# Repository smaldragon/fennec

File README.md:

# fennec
An Homebrew computer using the 65c02 CPU.

All assembly code is built using my custom assembler built for personal hobby use, [CapyAsm](https://github.com/smaldragon/CapyASM), these two projects are closely linked and build off eachother, *with both* currently being in a early alpha state subject to bugs and regular breaking changes.

Documentation for the machine is located on its wiki at https://fennec6502.miraheze.org/

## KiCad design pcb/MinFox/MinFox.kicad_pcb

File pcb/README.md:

# GENERAL WARNING

These are various kicad projects developed over the course of this project, before taking a look at these it is extremely important that you understand the following:

* These projects are largely untested
* These projects were designed by a very clueless self-taught hobbyist
* I do not recommend using any of these for any purpose without scrutiny

## The projects

### 40key BreadKeys

A 40% mechanical keyboard matrix (8x5) designed to be hooked up to a breadboard via DuPont jumpers.

### MinFox 

A minimal expandable 65c02 sbc built for debugging peripherals, it contains ROM, RAM and 6 "slot select" lines (same terminology as the Fennec) that allow easily adding expansion chips without extra hardress decoding logic.

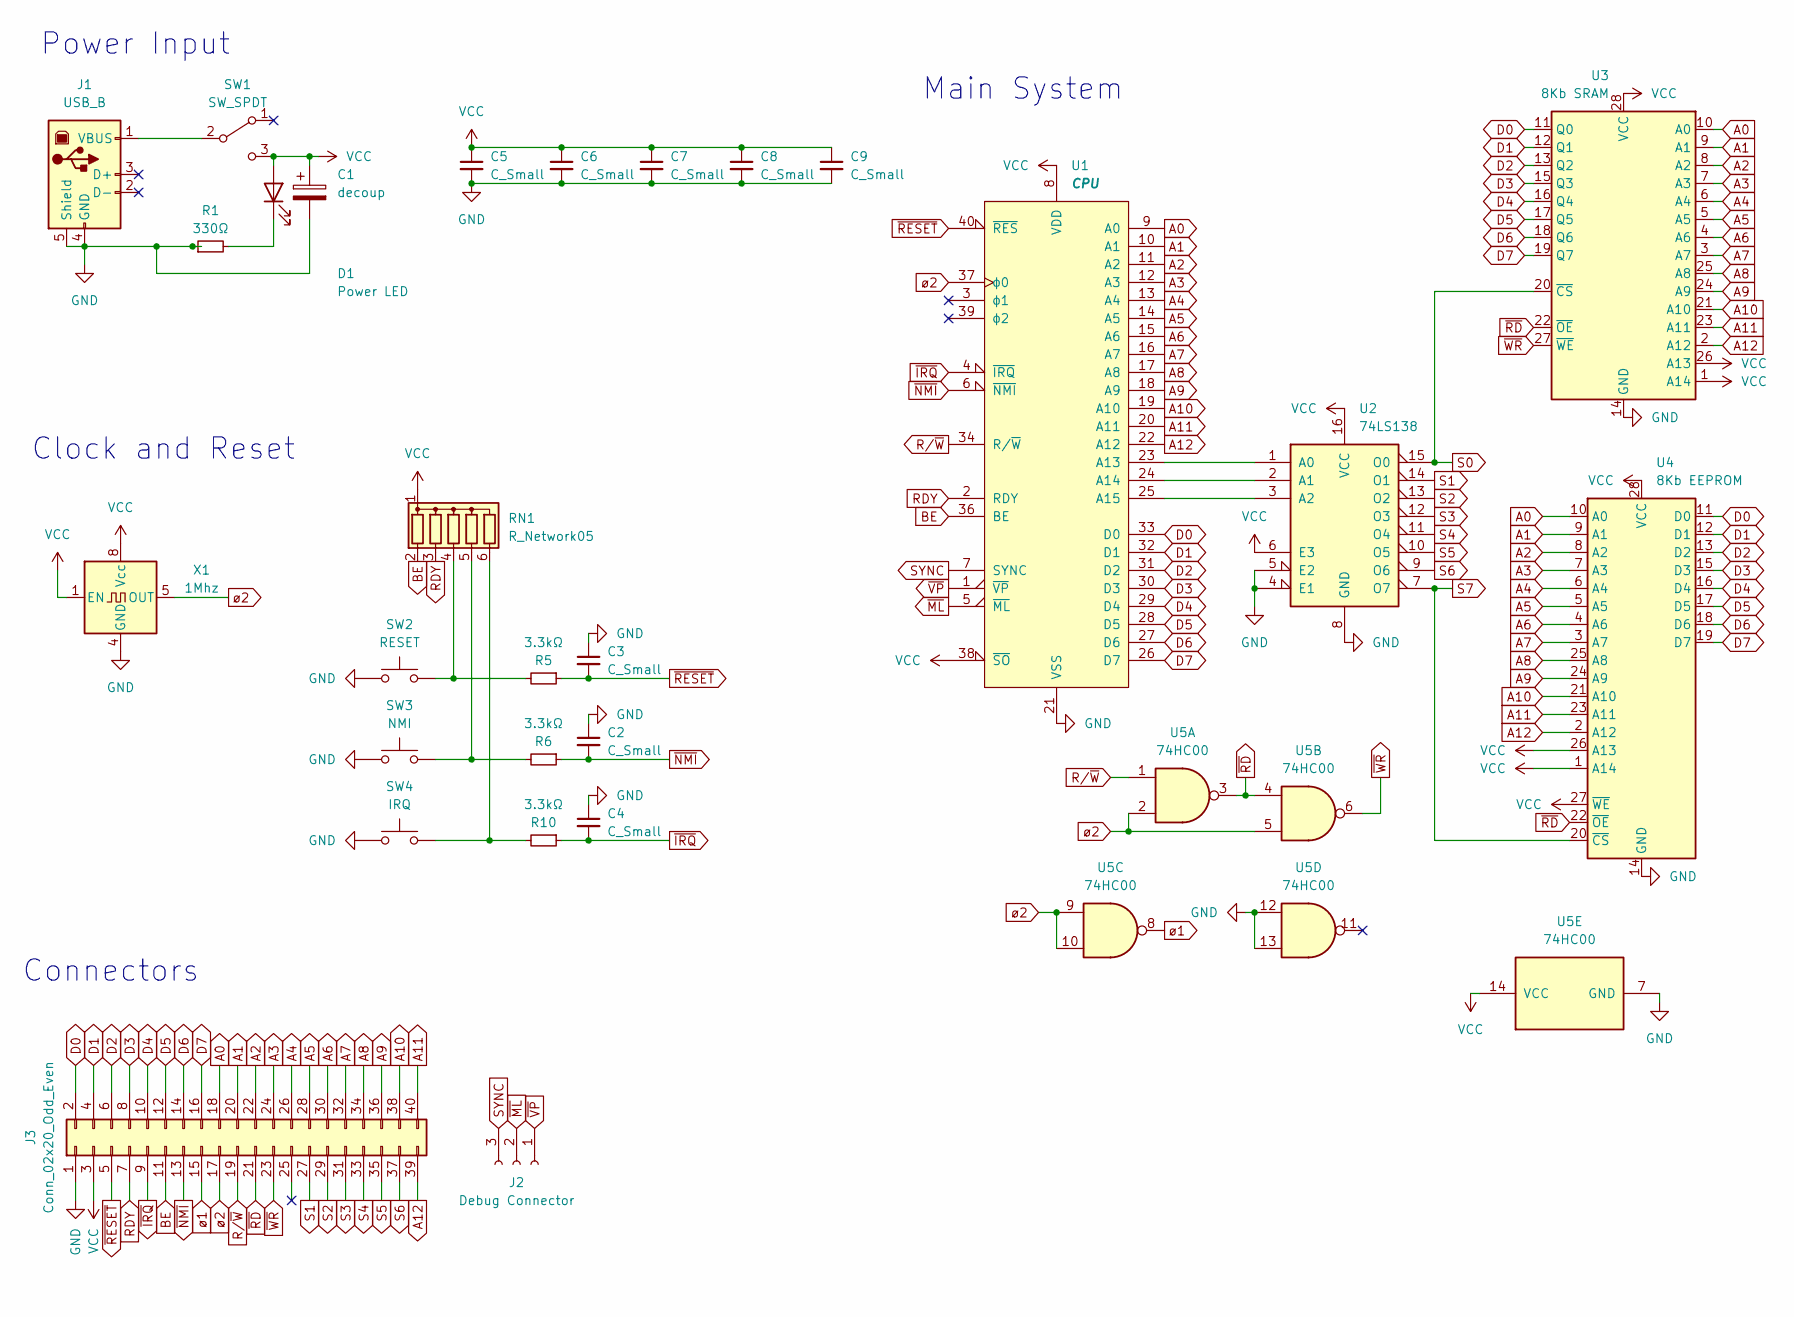
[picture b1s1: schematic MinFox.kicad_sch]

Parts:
C1: decoup; CP_Radial_D4.0mm_P1.50mm
C2, C3, C4, C5, C6, C7, C8, C9: C_Small; C_Disc_D3.0mm_W1.6mm_P2.50mm
D1: Power LED; LED_D5.0mm
J1: USB_B; USB_B_OST_USB-B1HSxx_Horizontal
J2: Debug Connector; PinSocket_1x03_P2.54mm_Vertical
J3: Conn_02x20_Odd_Even; PinSocket_2x20_P2.54mm_Vertical
R1: 330Ω; R_Axial_DIN0204_L3.6mm_D1.6mm_P5.08mm_Horizontal
R5, R6, R10: 3.3kΩ; R_Axial_DIN0204_L3.6mm_D1.6mm_P5.08mm_Horizontal
RN1: R_Network05; R_Array_SIP6
SW1: SW_SPDT; PinSocket_1x03_P2.54mm_Vertical
SW2: RESET; SW_PUSH_6mm
SW3: NMI; SW_PUSH_6mm
SW4: IRQ; SW_PUSH_6mm
U1: CPU; DIP-40_W15.24mm_Socket
U2: 74LS138; DIP-16_W7.62mm_Socket
U3: 8Kb SRAM; DIP-28_W15.24mm_Socket
U4: 8Kb EEPROM; DIP-28_W15.24mm_Socket
U5: 74HC00; DIP-14_W7.62mm_Socket
X1: 1Mhz; Oscillator_DIP-8

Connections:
A0: J3.18, U1.9 (A0), U3.10 (A0), U4.10 (A0)
A1: J3.20, U1.10 (A1), U3.9 (A1), U4.9 (A1)
A2: J3.22, U1.11 (A2), U3.8 (A2), U4.8 (A2)
A3: J3.24, U1.12 (A3), U3.7 (A3), U4.7 (A3)
A4: J3.26, U1.13 (A4), U3.6 (A4), U4.6 (A4)
A5: J3.28, U1.14 (A5), U3.5 (A5), U4.5 (A5)
A6: J3.30, U1.15 (A6), U3.4 (A6), U4.4 (A6)
A7: J3.32, U1.16 (A7), U3.3 (A7), U4.3 (A7)
A8: J3.34, U1.17 (A8), U3.25 (A8), U4.25 (A8)
A9: J3.36, U1.18 (A9), U3.24 (A9), U4.24 (A9)
A10: J3.38, U1.19 (A10), U3.21 (A10), U4.21 (A10)
A11: J3.40, U1.20 (A11), U3.23 (A11), U4.23 (A11)
A12: J3.39, U1.22 (A12), U3.2 (A12), U4.2 (A12)
BE: J3.11, RN1.2 (R1), U1.36 (BE)
D0: J3.2, U1.33 (D0), U3.11 (Q0), U4.11 (D0)
D1: J3.4, U1.32 (D1), U3.12 (Q1), U4.12 (D1)
D2: J3.6, U1.31 (D2), U3.13 (Q2), U4.13 (D2)
D3: J3.8, U1.30 (D3), U3.15 (Q3), U4.15 (D3)
D4: J3.10, U1.29 (D4), U3.16 (Q4), U4.16 (D4)
D5: J3.12, U1.28 (D5), U3.17 (Q5), U4.17 (D5)
D6: J3.14, U1.27 (D6), U3.18 (Q6), U4.18 (D6)
D7: J3.16, U1.26 (D7), U3.19 (Q7), U4.19 (D7)
GND: C1.2, C2.1, C3.1, C4.1, C5.2, C6.2, C7.2, C8.2, C9.2, J1.4 (GND), J1.5 (Shield), J3.1, R1.1, SW2.1, SW3.1, SW4.1, U1.21 (VSS), U2.4 (E1), U2.5 (E2), U2.8 (GND), U3.14 (GND), U4.14 (GND), U5.7 (GND), U5.12, U5.13, X1.4 (GND)
unnamed: D1.1 (K), R1.2
unnamed: J1.1 (VBUS), SW1.2 (B)
unnamed: R5.2, RN1.4 (R3), SW2.2
unnamed: R6.2, RN1.5 (R4), SW3.2
unnamed: R10.2, RN1.6 (R5), SW4.2
unnamed: U1.23 (A13), U2.1 (A0)
unnamed: U1.24 (A14), U2.2 (A1)
unnamed: U1.25 (A15), U2.3 (A2)
RDY: J3.7, RN1.3 (R2), U1.2 (RDY)
R/~W: J3.19, U1.34 (R/~W), U5.1
S0: U2.15 (O0), U3.20 (~CS)
S1: J3.27, U2.14 (O1)
S2: J3.29, U2.13 (O2)
S3: J3.31, U2.12 (O3)
S4: J3.33, U2.11 (O4)
S5: J3.35, U2.10 (O5)
S6: J3.37, U2.9 (O6)
S7: U2.7 (O7), U4.20 (~CS)
SYNC: J2.3, U1.7 (SYNC)
VCC: C1.1, C5.1, C6.1, C7.1, C8.1, C9.1, D1.2 (A), J3.3, RN1.1 (common), SW1.3 (C), U1.8 (VDD), U1.38 (~SO), U2.6 (E3), U2.16 (VCC), U3.1 (A14), U3.26 (A13), U3.28 (VCC), U4.1 (A14), U4.26 (A13), U4.27 (~WE), U4.28 (VCC), U5.14 (VCC), X1.1 (EN), X1.8 (Vcc)
~IRQ: C4.2, J3.9, R10.1, U1.4 (~IRQ)
~ML: J2.2, U1.5 (~ML)
~NMI: C2.2, J3.13, R6.1, U1.6 (~NMI)
~RD: J3.21, U3.22 (~OE), U4.22 (~OE), U5.3, U5.4
~RESET: C3.2, J3.5, R5.1, U1.40 (~RES)
~VP: J2.1, U1.1 (~VP)
~WR: J3.23, U3.27 (~WE), U5.6
ø1: J3.15, U5.8
ø2: J3.17, U1.37 (ϕ0), U5.2, U5.5, U5.9, U5.10, X1.5 (OUT)

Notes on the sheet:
Clock and Reset
Main System
Power Input
Connectors

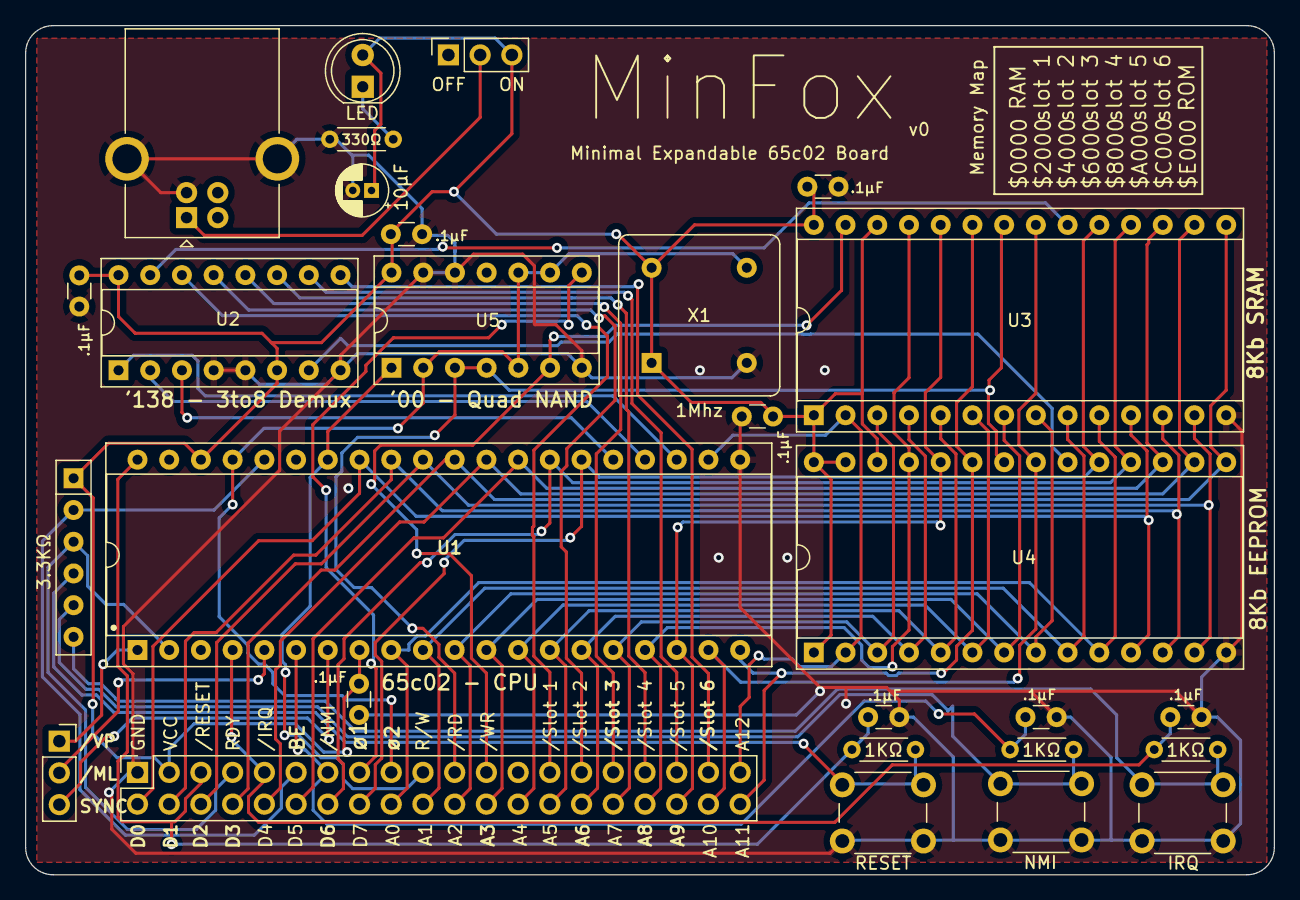
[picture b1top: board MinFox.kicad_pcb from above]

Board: 2 copper layers, 100.0 x 68.0 mm, 28 parts (0 on the bottom side), 52 nets.

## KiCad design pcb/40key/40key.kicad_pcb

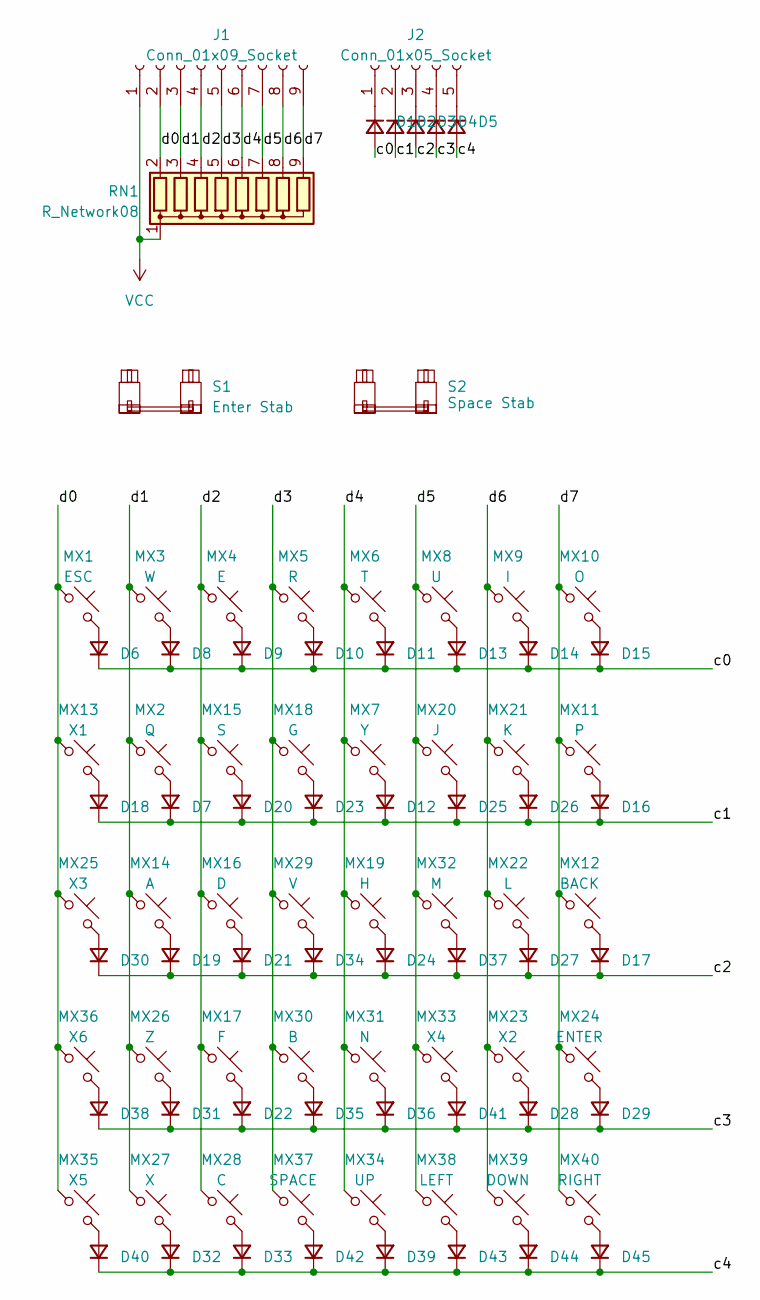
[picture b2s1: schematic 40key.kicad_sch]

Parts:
D1, D2, D3, D4, D5, D6, D7, D8, D9, D10, D11, D12, D13, D14, D15, D16, D17, D18, D19, D20, D21, D22, D23, D24, D25, D26, D27, D28, D29, D30, D31, D32, D33, D34, D35, D36, D37, D38, D39, D40, D41, D42, D43, D44, D45: D_Small; D_DO-34_SOD68_P7.62mm_Horizontal
J1: Conn_01x09_Socket; PinHeader_1x09_P2.54mm_Vertical
J2: Conn_01x05_Socket; PinSocket_1x05_P2.54mm_Vertical
MX1: ESC; SW_MX_1u
MX2: Q; SW_MX_1u
MX3: W; SW_MX_1u
MX4: E; SW_MX_1u
MX5: R; SW_MX_1u
MX6: T; SW_MX_1u
MX7: Y; SW_MX_1u
MX8: U; SW_MX_1u
MX9: I; SW_MX_1u
MX10: O; SW_MX_1u
MX11: P; SW_MX_1u
MX12: BACK; SW_MX_1.25u
MX13: X1; SW_MX_1.25u
MX14: A; SW_MX_1u
MX15: S; SW_MX_1u
MX16: D; SW_MX_1u
MX17: F; SW_MX_1u
MX18: G; SW_MX_1u
MX19: H; SW_MX_1u
MX20: J; SW_MX_1u
MX21: K; SW_MX_1u
MX22: L; SW_MX_1u
MX23: X2; SW_MX_1u
MX24: ENTER; SW_MX_1u
MX25: X3; SW_MX_1.75u
MX26: Z; SW_MX_1u
MX27: X; SW_MX_1u
MX28: C; SW_MX_1u
MX29: V; SW_MX_1u
MX30: B; SW_MX_1u
MX31: N; SW_MX_1u
MX32: M; SW_MX_1u
MX33: X4; SW_MX_1.5u
MX34: UP; SW_MX_1u
MX35: X5; SW_MX_1.25u
MX36: X6; SW_MX_1.75u
MX37: SPACE; SW_MX_1u
MX38: LEFT; SW_MX_1u
MX39: DOWN; SW_MX_1u
MX40: RIGHT; SW_MX_1u
RN1: R_Network08; R_Array_SIP9
S1: Enter Stab; STAB_MX_2u
S2: Space Stab; STAB_MX_6.25u

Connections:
/c0: D1.2 (A), D6.1 (K), D8.1 (K), D9.1 (K), D10.1 (K), D11.1 (K), D13.1 (K), D14.1 (K), D15.1 (K)
/c1: D2.2 (A), D7.1 (K), D12.1 (K), D16.1 (K), D18.1 (K), D20.1 (K), D23.1 (K), D25.1 (K), D26.1 (K)
/c2: D3.2 (A), D17.1 (K), D19.1 (K), D21.1 (K), D24.1 (K), D27.1 (K), D30.1 (K), D34.1 (K), D37.1 (K)
/c3: D4.2 (A), D22.1 (K), D28.1 (K), D29.1 (K), D31.1 (K), D35.1 (K), D36.1 (K), D38.1 (K), D41.1 (K)
/c4: D5.2 (A), D32.1 (K), D33.1 (K), D39.1 (K), D40.1 (K), D42.1 (K), D43.1 (K), D44.1 (K), D45.1 (K)
/d0: J1.2, MX1.1, MX13.1, MX25.1, MX35.1, MX36.1, RN1.2 (R1)
/d1: J1.3, MX2.1, MX3.1, MX14.1, MX26.1, MX27.1, RN1.3 (R2)
/d2: J1.4, MX4.1, MX15.1, MX16.1, MX17.1, MX28.1, RN1.4 (R3)
/d3: J1.5, MX5.1, MX18.1, MX29.1, MX30.1, MX37.1, RN1.5 (R4)
/d4: J1.6, MX6.1, MX7.1, MX19.1, MX31.1, MX34.1, RN1.6 (R5)
/d5: J1.7, MX8.1, MX20.1, MX32.1, MX33.1, MX38.1, RN1.7 (R6)
/d6: J1.8, MX9.1, MX21.1, MX22.1, MX23.1, MX39.1, RN1.8 (R7)
/d7: J1.9, MX10.1, MX11.1, MX12.1, MX24.1, MX40.1, RN1.9 (R8)
unnamed: D1.1 (K), J2.1
unnamed: D2.1 (K), J2.2
unnamed: D3.1 (K), J2.3
unnamed: D4.1 (K), J2.4
unnamed: D5.1 (K), J2.5
unnamed: D6.2 (A), MX1.2
unnamed: D7.2 (A), MX2.2
unnamed: D8.2 (A), MX3.2
unnamed: D9.2 (A), MX4.2
unnamed: D10.2 (A), MX5.2
unnamed: D11.2 (A), MX6.2
unnamed: D12.2 (A), MX7.2
unnamed: D13.2 (A), MX8.2
unnamed: D14.2 (A), MX9.2
unnamed: D15.2 (A), MX10.2
unnamed: D16.2 (A), MX11.2
unnamed: D17.2 (A), MX12.2
unnamed: D18.2 (A), MX13.2
unnamed: D19.2 (A), MX14.2
unnamed: D20.2 (A), MX15.2
unnamed: D21.2 (A), MX16.2
unnamed: D22.2 (A), MX17.2
unnamed: D23.2 (A), MX18.2
unnamed: D24.2 (A), MX19.2
unnamed: D25.2 (A), MX20.2
unnamed: D26.2 (A), MX21.2
unnamed: D27.2 (A), MX22.2
unnamed: D28.2 (A), MX23.2
unnamed: D29.2 (A), MX24.2
unnamed: D30.2 (A), MX25.2
unnamed: D31.2 (A), MX26.2
unnamed: D32.2 (A), MX27.2
unnamed: D33.2 (A), MX28.2
unnamed: D34.2 (A), MX29.2
unnamed: D35.2 (A), MX30.2
unnamed: D36.2 (A), MX31.2
unnamed: D37.2 (A), MX32.2
unnamed: D38.2 (A), MX36.2
unnamed: D39.2 (A), MX34.2
unnamed: D40.2 (A), MX35.2
unnamed: D41.2 (A), MX33.2
unnamed: D42.2 (A), MX37.2
unnamed: D43.2 (A), MX38.2
unnamed: D44.2 (A), MX39.2
unnamed: D45.2 (A), MX40.2
VCC: J1.1, RN1.1 (common)

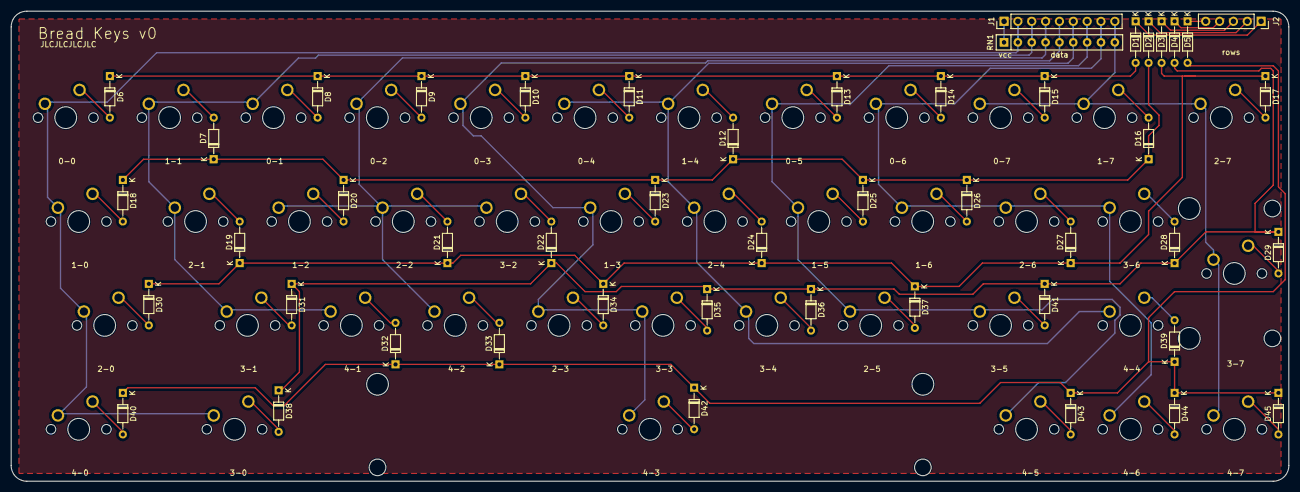
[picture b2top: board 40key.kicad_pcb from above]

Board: 2 copper layers, 234.3 x 86.2 mm, 90 parts (0 on the bottom side), 59 nets.

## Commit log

2023-05-16 Add Unilicense LICENSE
2023-05-16 add source files
2023-05-25 Add sd card loading and booting
2023-05-25 add font info to the src/ README.md
2023-05-29 fix boot rom
2023-06-30 add pcbs
